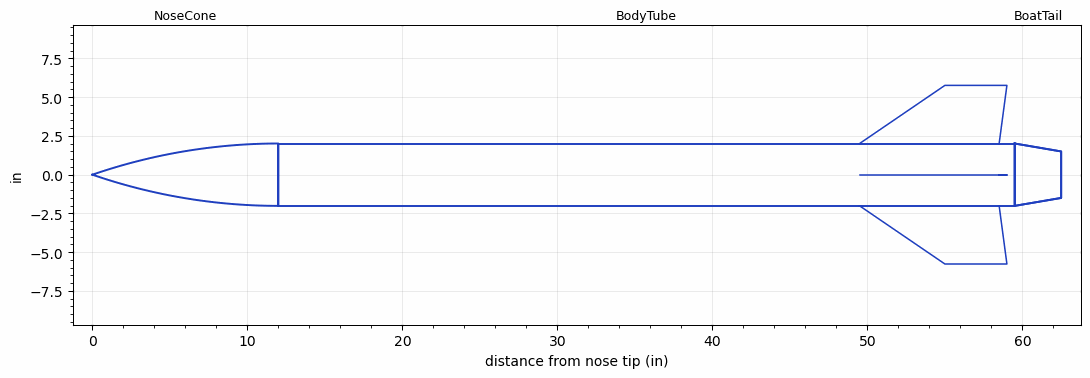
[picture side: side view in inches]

<RASAeroDocument>
 <FileVersion>2</FileVersion>
 <RocketDesign>
  <NoseCone>
   <Length>12</Length>
   <Diameter>4.024</Diameter>
   <Shape>Tangent Ogive</Shape>
   <Location>0</Location>
  </NoseCone>
  <BodyTube>
   <Length>47.5</Length>
   <Diameter>4.024</Diameter>
   <RailGuideDiameter>0.381</RailGuideDiameter>
   <RailGuideHeight>0.38</RailGuideHeight>
   <Location>12</Location>
   <BoattailLength>3</BoattailLength>
   <BoattailRearDiameter>3</BoattailRearDiameter>
   <Fin>
    <Count>4</Count>
    <Chord>9</Chord>
    <Span>3.75</Span>
    <SweepDistance>5.5</SweepDistance>
    <TipChord>4</TipChord>
    <Thickness>0.25</Thickness>
    <Location>10</Location>
    <AirfoilSection>Hexagonal Blunt Base</AirfoilSection>
    <FX1>0.25</FX1>
    <FX3>0.25</FX3>
   </Fin>
  </BodyTube>
  <BoatTail>
   <Length>3</Length>
   <Diameter>4.024</Diameter>
   <RearDiameter>3</RearDiameter>
   <Location>59.5</Location>
  </BoatTail>
  <Surface>Camouflage Paint</Surface>
  <ModifiedBarrowman>True</ModifiedBarrowman>
  <Turbulence>False</Turbulence>
  <UseBooster1>False</UseBooster1>
  <UseBooster2>False</UseBooster2>
  <Comments>L2 Design
J410-7 Cesaroni Pro-38X Motor
64 inch total length configuration</Comments>
 </RocketDesign>
 <LaunchSite>
  <Altitude>876</Altitude>
  <Pressure>0</Pressure>
  <RodAngle>0</RodAngle>
  <RodLength>6</RodLength>
  <Temperature>50</Temperature>
  <WindSpeed>12</WindSpeed>
 </LaunchSite>
 <Recovery>
  <Altitude1>1000</Altitude1>
  <Altitude2>600</Altitude2>
  <DeviceType1>Parachute</DeviceType1>
  <DeviceType2>Parachute</DeviceType2>
  <Event1>True</Event1>
  <Event2>True</Event2>
  <Size1>24</Size1>
  <Size2>36</Size2>
  <EventType1>Apogee</EventType1>
  <EventType2>Altitude</EventType2>
  <CD1>0.97</CD1>
  <CD2>0.97</CD2>
 </Recovery>
 <SimulationList>
  <Simulation>
   <SustainerEngine>J410-16A  (CTI)</SustainerEngine>
   <SustainerLaunchWt>8.78</SustainerLaunchWt>
   <SustainerCG>33.5</SustainerCG>
   <SustainerIgnitionDelay>0</SustainerIgnitionDelay>
   <Booster1SeparationDelay>0</Booster1SeparationDelay>
   <Booster1IgnitionDelay>0</Booster1IgnitionDelay>
   <IncludeBooster1>False</IncludeBooster1>
   <Booster2Delay>0</Booster2Delay>
   <IncludeBooster2>False</IncludeBooster2>
   <TimetoApogee>14.18023</TimetoApogee>
   <MaxAltitude>3458.229</MaxAltitude>
   <MaxVelocity>570.6697</MaxVelocity>
  </Simulation>
 </SimulationList>
</RASAeroDocument>
